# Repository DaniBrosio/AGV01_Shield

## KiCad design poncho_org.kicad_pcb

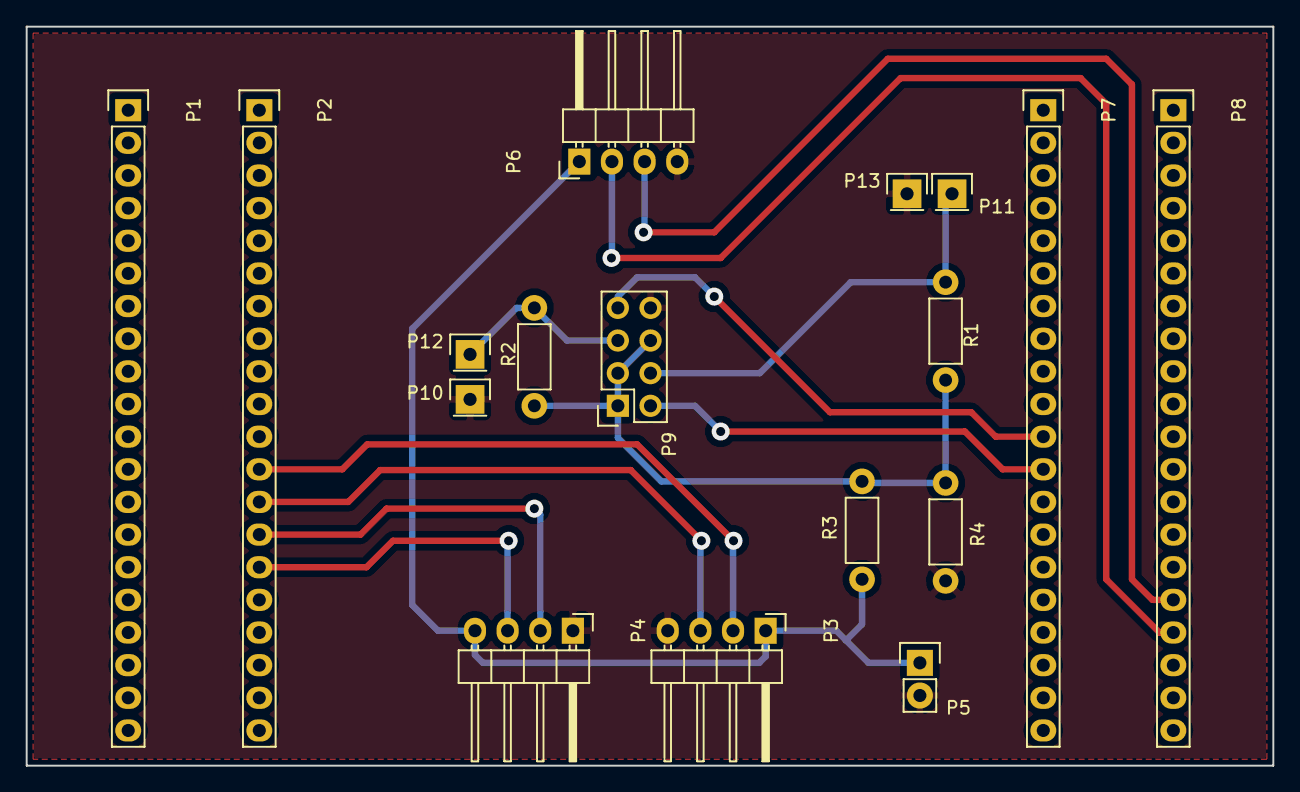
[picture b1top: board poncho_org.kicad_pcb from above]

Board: 2 copper layers, 97.0 x 57.5 mm, 17 parts (0 on the bottom side), 13 nets.

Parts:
P1, P2, P7, P8: CONN_01X20; Socket_Strip_Straight_1x20
P3, P4, P6: CONN_01X04; Pin_Header_Angled_1x04
P5: CONN_01X02; Pin_Header_Straight_1x02
P9: CONN_02X04; Socket_Strip_Straight_2x04
P10, P11, P12, P13: CONN_01X01; Pin_Header_Straight_1x01
R1, R2, R4: 4.7k; Resistor_Horizontal_RM7mm
R3: 10k; Resistor_Horizontal_RM7mm

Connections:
/+3.3V: P9.1, P9.3, P9.6, R1.1, R2.1, R3.2, R4.1
/CH_PD: P9.5, P12.1, R2.2
/GPIO0: P9.4, P11.1, R1.2
/echo: P6.3, P8.16
/intL: P2.14, P4.2
/intR: P2.15, P4.3
/linL: P2.12, P3.2
/linR: P2.13, P3.3
/rx_232: P7.11, P9.7
/trigger: P6.2, P8.17
/tx_232: P7.12, P9.2
GND: P3.4, P4.1, P5.2, P6.4, P9.8, P10.1, P13.1, R4.2
VCC: P3.1, P4.4, P5.1, P6.1, R3.1

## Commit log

2016-12-18 Initial commit Divisor de tension a 3.3 v corregido
